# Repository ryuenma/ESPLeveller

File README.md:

# ESP Leveller

A real-time steadiness game built on an **ESP32-C3** and an accelerometer sensor pod. Hold the device level; the moment it tilts past your threshold, the timer stops and you lose. Your phone is the controller *and* the display, over a self-hosted web interface with no app and no internet connection.

## Features

- **Real-time web UI**: timer, live tilt bar, and threshold control (slider and ± buttons), pushed over **Server-Sent Events at 10 Hz**
- **Random countdown** of 2 to 5 s, so you cannot pre-empt the start
- **Audio cues** generated on the phone itself (WebAudio): start beep, proximity ticking as you approach the limit, and a fail alarm
- **Threshold from 5 to 90°**, anywhere from "steady surgeon" to "anything goes"
- **Calibration**: whatever orientation you are holding becomes level, saved to flash
- **Settings persist** in NVS (threshold and calibration base), so they survive power cycles
- **Auto-detecting sensor pod**: detects a GY-521 (MPU6050) *or* a BMI160 breakout (e.g. GY-BMI160) at boot and picks the right driver. Marketplace "GY-LSM6DS3" boards often actually carry a BMI160, since the chips are pin-compatible; the firmware identifies the real chip by its ID register, so the label does not matter. See [Tested and proven](#tested-and-proven) before choosing a pod
- **Spectral spectator mode**: a second phone or laptop on the same network sees the round live

## Tested and proven

Honest status per path, because the two sensor paths are not equally proven and the README used to imply they were.

| Path | Status |
|---|---|
| **GY-521 (MPU6050)** | **Field-tested.** This is the path that ran on real devices, and it is where the drift bug was found and fixed. |
| **GY-BMI160** | **Written and committed, never run on hardware.** Do not trust it yet. |

Details:

- **The GY-521 path is proven in the field.** Commit `8781fb7` ("QC round 1", 2026-09-06) fixed a
  threshold bypass that turned out to be gyro bias accumulating over hours, which the commit
  records as *field-confirmed*. Tilt is now computed with `atan2` against gravity from the
  accelerometer, so it is absolute and does not drift.
- **The BMI160 path has never been on a real BMI160.** It landed in `823e704` on 2026-09-08,
  two days *after* the last field QC, and nothing since has put it on a sensor. The driver is
  written from the datasheet and reads plausibly, but "written" and "verified" are different
  claims and only the first one is true here. The soft reset and its dummy-read quirk, the
  100 Hz and ±2 g configuration, and the `CHIP_ID` detection are all unexercised.
- **No firmware release has been compiled in CI.** There is no build step in this repository
  and no `arduino-cli` on the machine that produced the release commits, so the firmware has
  never been built automatically. It was compiled and flashed by hand during development.
- **The web UI is verified against a mock, not a device.** The click-through in `anti-slop/`
  drives the real embedded page in headless Chromium against a Python mock of the firmware's
  HTTP surface. That proves the page, the state machine, and the SSE contract. It cannot prove
  real accelerometer noise, the WiFi access point, or the I2C bus. See
  [`anti-slop/README.md`](anti-slop/README.md).

If you are wiring this up for the first time, **start with a GY-521 (MPU6050)**. If you only have
a BMI160 pod, treat it as an untested code path and expect to debug it yourself. Reporting what
you find would be genuinely useful.

## Hardware

| Part | Role | Status |
|------|------|--------|
| ESP32-C3 (Super Mini / LuatOS C3-CORE or clone) | MCU + WiFi access point | Field-tested |
| **GY-521 (MPU6050)** | Tilt sensing | **Field-tested, use this one** |
| GY-BMI160 breakout | Tilt sensing | Driver written, **never run on hardware** |

Both pods wire up the same way and both are auto-detected, but see
[Tested and proven](#tested-and-proven) before choosing. The short version: the MPU6050 path
has run on real devices, the BMI160 path has not run on any.

### Wiring

```
ESP32-C3          Sensor pod
--------          ----------
3V3      ----->   VCC
GND      ----->   GND
IO4      ----->   SDA
IO5      ----->   SCL
```

> **Board notes (LuatOS ESP32C3-CORE and clones):** external SPI flash uses GPIO11-17, so
> do not use those pins for peripherals. Onboard LEDs are D4=GPIO12 and D5=GPIO13
> (active-high); D4 is the game-status LED here. USB is a CH343 bridge, so set
> **USB CDC On Boot: Disabled** and **Flash Mode: DIO** in the IDE.
>
> **Power note:** the Super Mini's onboard regulator is small. TX power is capped to
> 8.5 dBm in firmware for stability. If you still see brownouts or disconnects, add a
> **100 µF low-ESR capacitor** across the board's 5V and GND.

## How to use

1. Power the device over USB.
2. Connect your phone to the WiFi network `ESPLevellerAP` (password `levelup123`).
3. Open **http://192.168.4.1**. On iOS you can also try `http://leveller.local`; most
   Android builds dropped `.local` name resolution, so use the IP there.
4. **CALIBRATE**: hold the device the way you will hold it during a round, then tap
   CALIBRATE. That orientation becomes level.
5. Set the **threshold** with the slider or the ± buttons. This is only accepted while
   IDLE, so you cannot change the rules mid-round.
6. Tap **START**. A random 2 to 5 s countdown runs, then the timer starts.
7. **Keep it level.** The tilt bar fills as you tilt, turning amber at 75% of the
   threshold and red at the threshold.
8. Tilt past the threshold and the round ends, showing your final time.
9. **STOP** ends a countdown or a running round early and shows the elapsed time.
   **BACK TO MENU** returns to the idle screen.

The page is responsive and works on a second phone or laptop as a live spectator.

## Building and flashing

1. Open `ESP_Leveller.ino` in the **Arduino IDE** (or build it with `arduino-cli`).
2. Install the libraries (Library Manager). [Credits and dependencies](#credits-and-dependencies)
   names each one and pins the versions this release was built against:
   - **ESP Async WebServer** 3.6.0, by Mathieu Carbou, a fork of Me-No-Dev's
   - **Async TCP** 3.3.2, same maintainer. The web server requires it; the sketch never includes it directly
   - **MPU6050_tockn** 1.5.2, **only** if your pod is a GY-521 / MPU6050. A BMI160 pod needs no sensor library at all
3. Select **ESP32-C3 Dev Module** from the Espressif `esp32` platform (3.3.11 is what this
   release was verified against). On a LuatOS C3-CORE or any CH343 board, set
   **USB CDC On Boot: Disabled** and use **Flash Mode: DIO**.
4. Upload.

> **Serial logging** is compiled out by default (`ENABLE_SERIAL 0`) so a release build
> stays quiet on a headless kiosk. Define `ENABLE_SERIAL 1` at the top of the sketch to
> watch the boot sequence, sensor detection, and AP IP during bring-up.

## API

| Endpoint | Method | Description |
|----------|--------|-------------|
| `/` | GET | Web UI |
| `/api/events` | GET | SSE stream of `{"state","tilt","thr","t"}` at ~10 Hz |
| `/api/state` | GET | One-shot JSON state, used by the poll fallback |
| `/api/start` | POST | Start a countdown, or return to the menu from GAMEOVER |
| `/api/calibrate` | POST | Treat the current orientation as level |
| `/api/abort` | POST | Cancel a countdown, or end a running round and show the elapsed time |
| `/api/threshold?val=N` | POST | Set the threshold, clamped 5 to 90, accepted only while IDLE |

## Project layout

- `ESP_Leveller.ino`, the whole firmware in one sketch
- `DESIGN.md`, the web UI's design decisions and the reason behind each
- `anti-slop/`, the release audit and its click-through evidence
- `LICENSE`, MIT
- A custom carrier **PCB design** for a compact hardware build lives on the `pcb-design` branch.

## Credits and dependencies

### Firmware

Everything the device runs. Versions are the ones in the build this release was verified against, read from each library's own `library.properties`.

| Component | Version | Author | License | Role here |
|---|---|---|---|---|
| [ESP32 Arduino](https://github.com/espressif/arduino-esp32), the `esp32` platform | 3.3.11 | Espressif Systems | LGPL-2.1 | The MCU framework. Supplies `Wire.h`, `WiFi.h`, `Preferences.h`, `ESPmDNS.h`, `esp_wifi.h`, and the RISC-V toolchain, `esptool.py` and flasher that come with the package. |
| [ESP Async WebServer](https://github.com/mathieucarbou/ESPAsyncWebServer) | 3.6.0 | Me-No-Dev, maintained by Mathieu Carbou | LGPL-3.0 | `ESPAsyncWebServer.h`. The HTTP routes, and the `AsyncEventSource` behind `/api/events`. |
| [AsyncTCP](https://github.com/mathieucarbou/AsyncTCP) | 3.3.2 | Hristo Gochkov, maintained by Mathieu Carbou | LGPL-3.0 | Required by ESP Async WebServer, which declares `^3.3.2`. The sketch never includes it directly, but it does not build without it. |
| [MPU6050_tockn](https://github.com/tockn/MPU6050_tockn) | 1.5.2 | tockn, forked from [ElectronicCats/MPU6050](https://github.com/ElectronicCats/MPU6050) | **none declared**, see the note below | GY-521 / MPU6050 pods only. |

Two dependencies this project deliberately does **not** have:

- **No BMI160 driver.** The sketch reads the BMI160 configuration and data registers
  directly over I2C and identifies the chip from `CHIP_ID`. There is no Bosch library
  and no third-party BMI160 code anywhere in the project.
- **No ArduinoJson.** ESP Async WebServer advertises support for it, but the sketch
  formats its JSON with `snprintf` in `buildStateJson()`, so nothing pulls ArduinoJson in.

> **A caveat worth knowing about MPU6050_tockn.** The fork ships no `LICENSE` file and
> declares no `license=` field in its `library.properties`, so it carries no explicit
> grant to use or redistribute it. Its upstream, ElectronicCats' MPU6050, is MIT. Only
> the GY-521 path needs this library at all; a BMI160 pod builds without it. If you would
> rather sit on a plainly licensed library, ElectronicCats' original is API-compatible
> apart from its header name, so the swap is a one-line `#include` change.

### Web UI: none

The page embedded in `ESP_Leveller.ino` ships **no third-party code to the phone**. No
JavaScript framework, no CSS framework, no web fonts (the timer uses the browser's own
`monospace`, everything else uses `system-ui`), no CDN, no analytics, and no vendored
files. Audio is the browser's built-in WebAudio, and the live updates are the browser's
built-in `EventSource`. Every byte of the interface is written by hand in the sketch.

### Tooling

Build and audit only. None of this is on the device, and none of it is needed to run the firmware.

| Tool | License | Used for |
|---|---|---|
| Arduino IDE or `arduino-cli`, with Espressif's board package | LGPL-2.1 (with the package) | Compiling and flashing |
| [Node.js](https://nodejs.org) | MIT | Running the click-through harness |
| [playwright-core](https://github.com/microsoft/playwright) | Apache-2.0 | Driving headless Chromium |
| Chromium, Playwright build | BSD-3-Clause | Rendering the page under test |
| Python 3, standard library only | PSF | `anti-slop/mock-firmware-server.py` |

The dependencies above keep their own licences and are not redistributed here. Only the
firmware and the page in this repository are covered by [LICENSE](LICENSE).

## License

MIT, see [LICENSE](LICENSE).

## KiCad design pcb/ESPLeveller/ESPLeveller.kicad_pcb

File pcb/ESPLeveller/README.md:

# ESP Leveller — Custom PCB (P2: Layout)

**Status:** layout v2 — re-optimized placement (antenna overhang east edge + keepout, switch actuator facing board edge, real-body collision-free), Freerouting-routed (0 incomplete), GND pour on B.Cu, DRC 0 errors / 0 unconnected (5 silk warnings only), ERC 0 errors, netlist verified. All 12 components have 3D models for visual build preview (U1/U2/U3 use simplified box WRL placeholders — swap in vendor STEP models any time). Next: fab export (P3: Gerbers/drill/BOM).

Board: 105 × 75 mm, 2-layer. Signal flow left→right: TP4056 (USB charge, connector overhanging left edge) → power switch (actuator faces top edge) → MT3608 (5V boost) → SuperMini socket (antenna section overhangs right edge + copper keepout). Sensor pod socket + I2C pull-ups top-right, status LED + opt button bottom-right, battery header bottom-left.

## Files

| File | What |
|---|---|
| `ESPLeveller.kicad_pcb` | Board layout (KiCad 10) |
| `p2_populate.py` / `p2_route.py` / `p2_zone.py` / `p2_fill.py` | Reproducible layout pipeline (pcbnew API → Freerouting → zone fill) |
| `footprints/3d/*.wrl` | Simple 3D models for the module footprints |
| `p2_drc_final9.rpt` / `p2_erc8.rpt` / `p2_verify.net` | Final verification artifacts |
| `p2_assembled_top.png` / `p2_assembled_bottom.png` | Assembled 3D renders |

## Design

Drop-in carrier board — all active electronics are cheap replaceable modules, everything else is through-hole. **Zero SMD soldering required.**

```
2x 18650 (parallel) ──► TP4056 module (charge+protect) ──► slide SW ──► MT3608 boost (5.0V) ──► ESP32-C3 Super Mini (5V pin)
                                                              │
                              100µF bulk cap on +5V rail ◄────┘
ESP32-C3 SuperMini IO4 (SDA) ──┬── GY-521 / LSM6DS3 pod socket (8-pin, 2.54mm)
                IO5 (SCL) ─────┤   + 4.7k pull-ups to 3V3
                IO6 ───────────┴── optional operator button (to GND)
                IO7 ── 330R ── green THT status LED ── GND
```

## Files

| File | What |
|---|---|
| `ESPLeveller.kicad_sch` | Schematic (KiCad 10) |
| `ESPLeveller.kicad_pro` | Project file |
| `symbols/ESPLeveller.kicad_sym` | Module symbols (SuperMini socket, TP4056, MT3608) |
| `symbols/Generic.kicad_sym` | R/C/LED/SW/conn/power symbols |
| `footprints/ESPLeveller.pretty/` | Custom footprints (socket + module pads) |
| `ESPLeveller.pdf` | Rendered schematic for quick review |
| `ESPLeveller.net` | Exported netlist |

## Assembly notes (future BOM)

| Part | Source | ~Cost |
|---|---|---|
| ESP32-C3 Super Mini | AliExpress | ~$2 |
| TP4056 module (with protection) | AliExpress | ~$0.50 |
| MT3608 boost module — **set to 5.0V BEFORE install** | AliExpress | ~$0.50 |
| 2× 18650 + holders (parallel) | local | ~$6 |
| GY-521 now / LSM6DS3TR-C breakout later | AliExpress | $1–3 |
| THT: 100µF cap, 2× 4.7k, 330R, green 5mm LED, SPST slide switch, 8-pin female socket, 2-pin headers | — | ~$1 |

## Before first power-up

1. **Verify MT3608 is set to 5.0V** with a multimeter (no load), using its own pot — overvoltage kills the Super Mini.
2. TP4056 module must be the **protected** version (DW01+FS8205) — with raw 18650s this is not optional.
3. Cells in parallel: charge both to the same voltage BEFORE connecting in parallel.

## Firmware pin map (matches `Barrett_Leveller` sketch)

| Function | GPIO |
|---|---|
| SDA | IO4 |
| SCL | IO5 |
| Optional STOP button | IO6 |
| Status LED | IO7 |

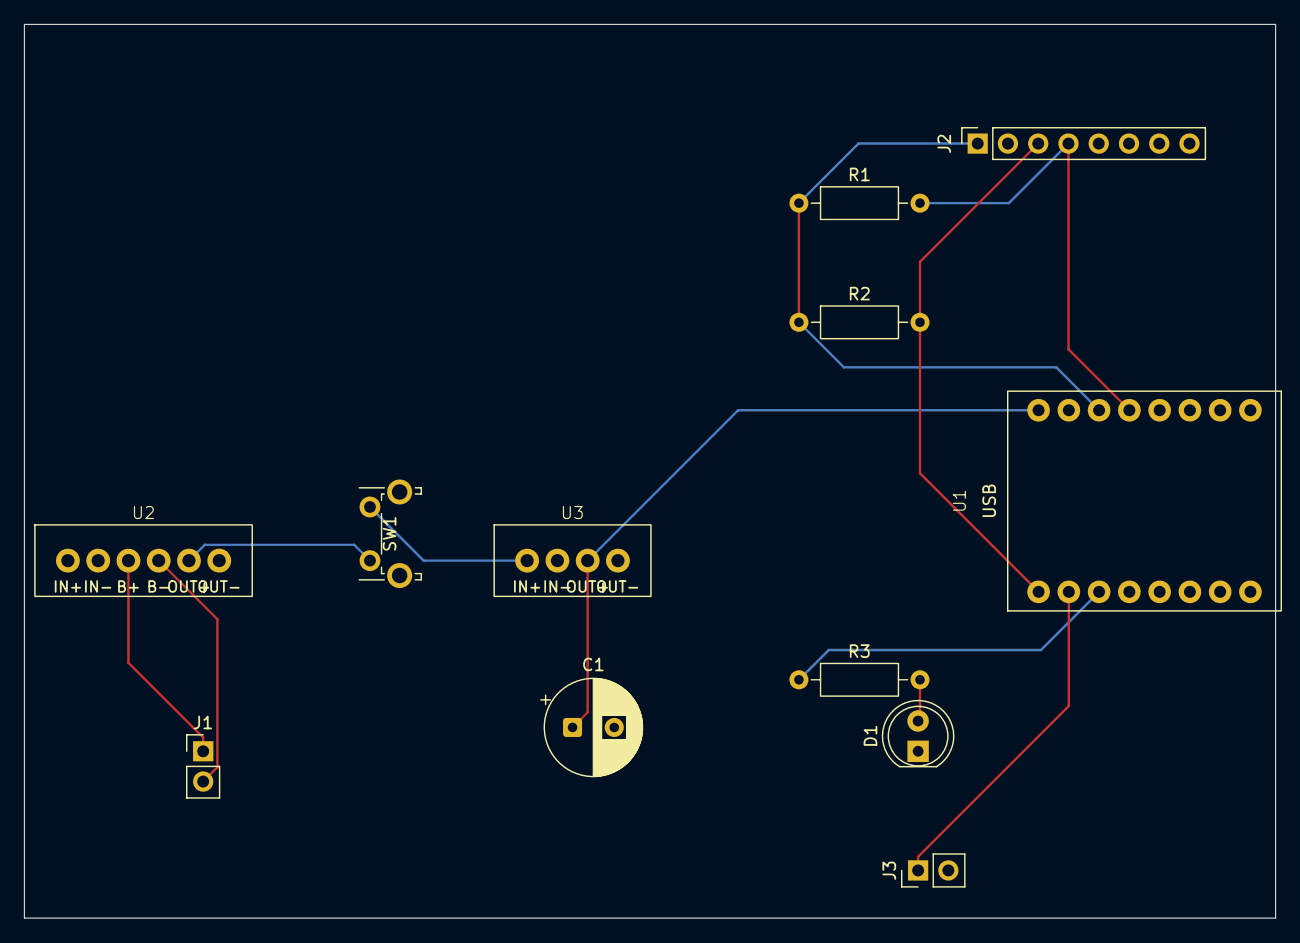
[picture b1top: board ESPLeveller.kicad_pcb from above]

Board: 2 copper layers, 105.0 x 75.0 mm, 12 parts (0 on the bottom side), 12 nets.

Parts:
C1: 100uF; CP_Radial_D8.0mm_P3.50mm
D1: STATUS_GREEN; LED_D5.0mm
J1: Battery_18650x2; PinHeader_1x02_P2.54mm_Vertical
J2: Sensor_Pod; PinSocket_1x08_P2.54mm_Vertical
J3: OPT_BTN; PinHeader_1x02_P2.54mm_Vertical
R1, R2: 4.7k; R_Axial_DIN0207_L6.3mm_D2.5mm_P10.16mm_Horizontal
R3: 330R; R_Axial_DIN0207_L6.3mm_D2.5mm_P10.16mm_Horizontal
SW1: PWR; SW_Tactile_SPST_Angled_PTS645Vx31-2LFS
U1: ESP32C3_SuperMini; ESP32-C3-SuperMini_Socket
U2: TP4056_ChargeProt; TP4056_Module_Pads
U3: MT3608_5V; MT3608_Module_Pads

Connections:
+3V3: J2.1, R1.1, R2.1, U1.6
+5V: C1.1, U1.8, U3.3
/BATT+: J1.1, U2.3
/BATT-: J1.2, U2.4
/BTN: J3.1, U1.10
/LED_STAT: R3.1, U1.11
/SCL: J2.3, R2.2, U1.9
/SDA: J2.4, R1.2, U1.5
GND: C1.2, D1.1, J2.2, J2.7, J3.2, U1.7, U2.6, U3.2, U3.4
unnamed: D1.2, R3.2
unnamed: SW1.1, U2.5
unnamed: SW1.2, U3.1
